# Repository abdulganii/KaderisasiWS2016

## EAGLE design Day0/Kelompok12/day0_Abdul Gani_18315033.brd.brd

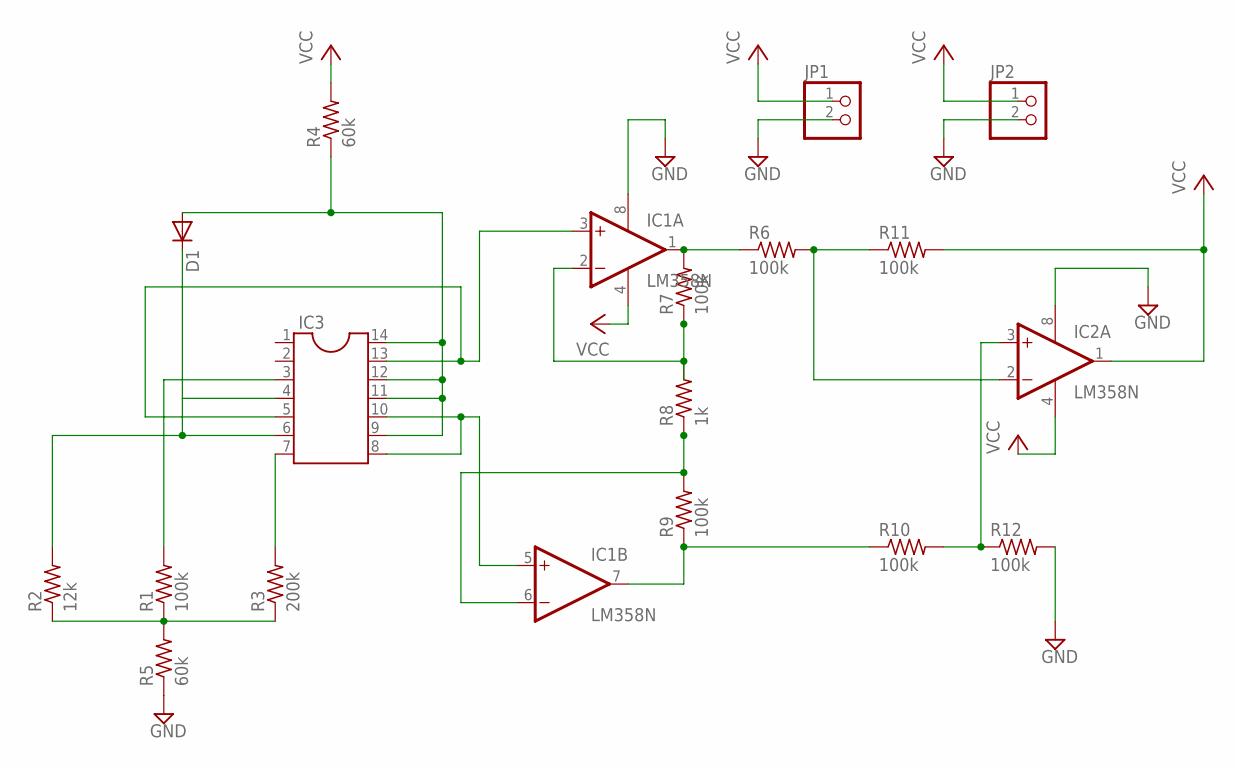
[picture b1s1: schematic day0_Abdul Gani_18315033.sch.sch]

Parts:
D1: DIODE-D-7.5; D-7.5
IC1, IC2: LM358N; DIL08
IC3: DIL14
JP1, JP2: PINHD-1X2; 1X02
R1, R6, R7, R9, R10, R11, R12: 100k; 0204/7
R2: 12k; 0204/7
R3: 200k; 0204/7
R4, R5: 60k; 0204/7
R8: 1k; 0204/7

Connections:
GND: IC1.8 (V+), IC2.8 (V+), JP1.2, JP2.2, R5.1, R12.2
unnamed: R1.1, R2.1, R3.1, R5.2
unnamed: R7.1, R8.2
unnamed: IC1.6 (-IN), R8.1, R9.2
unnamed: IC1.1 (OUT), R6.1, R7.2
unnamed: D1.C, IC3.4, IC3.6, R2.2
unnamed: IC3.7, R3.2
unnamed: IC3.3, R1.2
unnamed: D1.A, IC3.9, IC3.11, IC3.12, IC3.14, R4.1
unnamed: IC1.5 (+IN), IC3.8, IC3.10
unnamed: IC1.3 (+IN), IC3.5, IC3.13
unnamed: IC1.7 (OUT), R9.1, R10.1
unnamed: IC2.2 (-IN), R6.2, R11.1
unnamed: IC2.3 (+IN), R10.2, R12.1
VCC: IC1.4 (V-), IC2.1 (OUT), IC2.4 (V-), JP1.1, JP2.1, R4.2, R11.2

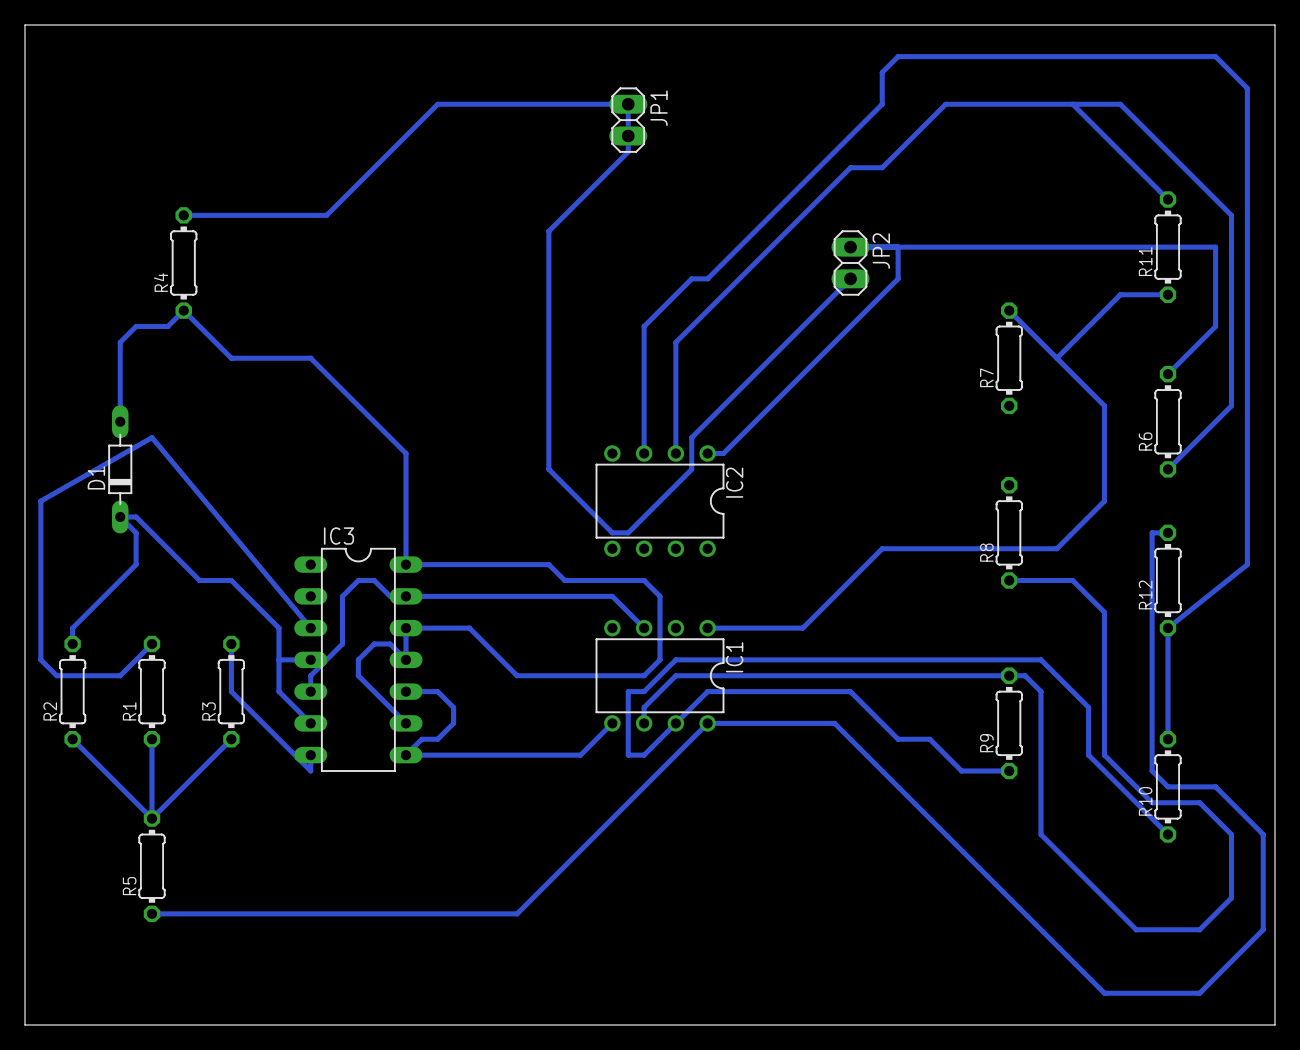
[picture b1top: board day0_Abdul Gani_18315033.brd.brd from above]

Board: 2 copper layers, 100.0 x 80.0 mm, 18 parts (0 on the bottom side), 15 nets.
